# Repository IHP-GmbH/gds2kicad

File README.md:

# gds2kicad

Turn a die or chiplet GDSII into the KiCad parts you need to design a board or
an interposer around it: footprints, schematic symbols, pin lists, and the
netlist that flows back into the chiplet assembly format.

KiCad cannot read GDS. The usual fallback is redrawing bond pads by hand from a
datasheet and typing pin names into a symbol cell by cell, then doing it again
every time the layout changes. gds2kicad reads the pad geometry and the text
labels straight out of the layout, so the KiCad part matches the silicon.

## Status

> [!WARNING]
> gds2kicad is currently a preview release only!

**Contents:** [Install](#install) - [Quick start](#quick-start) -
[Tools](#tools) - [Selecting layers](#selecting-layers) -
[Workflows](#workflows) - [Where files are written](#where-files-are-written) -
[Troubleshooting](#troubleshooting) - [Documentation](#documentation)

## Install

There is nothing to build and nothing to install: run the scripts from the
clone root. You need KLayout (reads the GDS) and PyQt6 (for the GUI).

```sh
python3 -m venv venv && source venv/bin/activate
pip install -r requirements.txt    # PyQt6, PyYAML
pip install klayout                # GDS reader
```

A system KLayout install with its Python bindings on `PYTHONPATH` works too. If
`import klayout.db` fails, the converters exit with a message saying so.
`pip install -e .` installs the same modules with all three dependencies,
klayout included (`pyproject.toml`).

Python 3.11 is the version CI runs. On a slim Linux box or container, PyQt6 also
needs `libgl1 libegl1 libxkbcommon0 libdbus-1-3 libfontconfig1 libglib2.0-0`, or
the GUI dies on a Qt platform-plugin error. To run the tests you additionally
need `pip install pytest`.

## Quick start

No GDS at hand? Both converters can write themselves a small one, which is the
quickest way to check the install:

```sh
python3 gds_to_kicad.py --generate-test-gds     # writes tests/test_footprint.gds
python3 gds_to_kicad.py tests/test_footprint.gds -o demo.kicad_mod
```

That gives you 3 pads. They come out numbered, not named, because the fixture
carries no text labels; a real GDS does.

### With the GUI

The simplest way in, and it drives the same engine as the command line:

```sh
python3 unified_gui.py
```

One window, five tabs in order: **Extract Pins** from a GDS, **Pin List Editor**
to fix names, sides and types, **Symbol Designer** with a live preview,
**Footprint Generator**, and a **History** of past runs.

On a headless machine, set `QT_QPA_PLATFORM=offscreen`.

### From the command line

```sh
python3 gds_to_kicad.py die.gds -o die.kicad_mod          # footprint
python3 gds_to_kicad_symbol.py die.gds -o die.kicad_sym   # symbol
```

With no layer flags both tools auto-detect the densest pad layer and the text
layer that names the pads. That works on a clean chiplet GDS. On a real full die
it will happily return routing, fill and guard rings as "pads", so read
[Selecting layers](#selecting-layers) and
[Curating pads by hand](#curating-pads-by-hand) before trusting the result.

## Tools

| Tool | Does |
| --- | --- |
| `unified_gui.py` | GUI covering the whole flow: pins, symbol, footprint |
| `gds_to_kicad.py` | GDS to `.kicad_mod` footprint |
| `gds_to_kicad_symbol.py` | GDS to `.kicad_sym` symbol library |
| `blackbox_chiplet.py` | Pad map (JSON or CSV) to a stand-in GDS |
| `footprint_to_pinlist.py` | `.kicad_mod` to pin list JSON |
| `kicad_netlist_to_chiplet.py` | KiCad `.net` to chiplet YAML, CSV or `.chiplet` |
| `chiplet_to_kicad_sch.py` | `.chiplet` system to a KiCad schematic, one symbol per die and per carrier pad, or to a symbol library and blank sheet |
| `kicad_sch_to_connectivity.py` | Netlist of an edited system schematic to a connectivity form |
| `kicad_sch_to_cosim_setup.py` | Netlists of edited co-simulation setup sheets to a setup form |
| `extract_padmap.py` | Plan a die's pad map, or extract it from a finished die GDS |
| `io_pads/generate_io_pad.py` | Parametric interposer I/O pad symbol and footprint |
| `io_pads/kicad_pcb_to_iopads.py` | Routed `.kicad_pcb` to `io_pads.json` |

Every tool accepts `--help`.

## Selecting layers

There is no PDK baked in, no `--pdk` flag and no PDK discovery. You always say
explicitly where the pads are, in one of three ways:

| Precedence | How | Example |
| --- | --- | --- |
| 1 | Raw GDS number, ignores the `.lyp` | `--pad-layer-number 134/0` |
| 2 | Layer name from a KLayout `.lyp` | `--lyp-file pdks/sg13g2.lyp --layer TopMetal2.drawing` |
| 3 | Nothing, auto-detect the densest pad layer | (no flags) |

Pin names come from a separate text layer, selected the same way:
`--text-layer NAME`, `--text-layer-number N/D`, or auto-detect.

> **Two things that will bite you.** First, the flag spelling differs between
> the converters: `gds_to_kicad.py` uses `--layer`, `gds_to_kicad_symbol.py`
> uses `--pad-layer`. The `*-layer-number` flags are the same on both.
>
> Second, and this one costs people an afternoon: if you name the pad layer with
> `--layer` and say nothing about text, `gds_to_kicad.py` emits **numbered**
> pads instead of named ones, silently. Add `--text-layer NAME`, or
> `--auto-text` to let it find the text layer itself. The symbol tool does not
> have this problem: it derives `TopMetal2.text` from `TopMetal2.drawing` on its
> own, which is why it has no `--auto-text` flag. When both tools auto-detect
> the pad layer, both auto-detect the text layer too.

### Bundled layer files

`pdks/` ships four ready `.lyp` files:

| File | Contents |
| --- | --- |
| `generic.lyp` | **Default.** Pads-only vocabulary: pad metal `205/0`, pad text `205/25`, outline `206/0`. For closed chiplets that ship no layer file. |
| `sg13g2.lyp` | Full IHP SG13G2 layer set, a byte copy of IHP-Open-PDK's, pinned to its source commit by `tests/test_sg13g2_lyp_source.py` |
| `sky130.lyp` | Full SkyWater sky130 layer set, a byte copy of open_pdks' `sky130/klayout/sky130.lyp` (Apache-2.0) |
| `interposer.lyp` | SG13G2 upper metals through Bump, for interposer work |

Any technology works: drop its KLayout `.lyp` into `pdks/`, or pass any path
with `--lyp-file`. IHP SG13G2 is what we test against most, not a requirement.

### Inspecting a GDS first

```sh
python3 gds_to_kicad.py die.gds --scan-layers                        # suggest pad/text candidates
python3 gds_to_kicad.py die.gds --list-layers --lyp-file pdks/sky130.lyp   # dump the parsed .lyp
```

## Workflows

### Die to footprint

```sh
python3 gds_to_kicad.py die.gds --lyp-file pdks/sg13g2.lyp \
    --layer TopMetal2.drawing --text-layer TopMetal2.text -o die.kicad_mod
```

Reads the top cell, flattens it, pulls box and polygon shapes off the pad layer,
and names each pad from the nearest text label. Rectangular pads become
`smd rect`; non-rectangular pads become `smd custom` with a `gr_poly` primitive,
so the real shape is preserved. It also writes a courtyard and traceability
properties recording the source GDS, the `.lyp`, the layer and the orientation
(`GDS_FILE`, `LYP_FILE`, `GDS_LAYER`, `ORIENTATION`).

For a die that mounts face-down on an interposer, add `--flip-chip` to mirror X
so the footprint reads as seen from the interposer side.

Die thickness is assembly metadata, not GDS geometry, so it is only written when
you pass it: `--die-thickness-um 300` emits a `DIE_THICKNESS_UM` property that
chiplet-export reads into hyp-to-gds `--die-thicknesses` for the assembly z-stack.
Omit it and the property is left out (the export defaults it to 0.0).

By default the courtyard is the pad bounding box, which for an inset pad ring is
smaller than the die. Name the layer that carries the die outline, for example
`--die-outline-layer 206/0` for a generic black-box die or `189/4` (prBoundary)
for an SG13G2 die built with LibreLane, and the courtyard becomes that outline.
The layer is also recorded as a `DIE_OUTLINE_LAYER` property (`"206/0"`), meant
for downstream tools that size the die from its GDS rather than from KiCad
geometry. The outline must merge to exactly one rectangle containing every pad;
anything else, no pads at all, or a `--dbu` that differs from the file's is an
error and no file is written. Omit the option and neither the
courtyard nor the properties change.

### Die to symbol

```sh
python3 gds_to_kicad_symbol.py die.gds --lyp-file pdks/sg13g2.lyp \
    --pad-layer TopMetal2.drawing -o die.kicad_sym
```

Same pad and text extraction, emitted as a KiCad 6+ `.kicad_sym`. Pins are
arranged automatically: power top and bottom, signals left and right. Extras:
`--symbol-name`, `--footprint-ref`, and `--max-text-distance` (a DBU cutoff for
matching text to pads).

There is a two-step path when the automatic result needs fixing. Dump an
editable pin list, correct names, sides and types, then rebuild from it with no
GDS involved:

```sh
python3 gds_to_kicad_symbol.py die.gds --extract-pins pins.json
python3 gds_to_kicad_symbol.py --from-pin-list pins.json -o die.kicad_sym
```

In that JSON each pin carries a `name`, a `side` (`left`, `right`, `top`,
`bottom`) and a `type` (`passive`, `input`, `output`, `bidirectional`,
`tri_state`, `power_in`, `power_out`, `unspecified`), plus its geometry in DBU.
The same file is what the Pin List Editor tab edits, and what `--pin-list`
expects in the pad-review workflow below.

### Curating pads by hand

This is the normal path for real silicon, not an advanced fallback. A full die
GDS is mostly routing, fill and guard rings, and auto-detect cannot tell those
from bond pads. Strip the GDS down to the pad layer plus labels, clean it up in
KLayout, then build from the result:

```sh
python3 gds_to_kicad.py die.gds --generate-pad-review review.gds
klayout -e -l pdks/sg13g2.lyp review.gds   # delete everything that is not a real pad, save
python3 gds_to_kicad.py --from-pad-review review.gds --pin-list pins.json -o die.kicad_mod
```

`--pin-list` is **required** here: it is the authoritative list of names, and
pads are matched to it by nearest neighbor, with warnings for anything left
unmatched. Produce it with `gds_to_kicad_symbol.py --extract-pins pins.json` or
with `footprint_to_pinlist.py`.

To keep the die outline on this path, pass the same `--die-outline-layer` to
both steps. `--generate-pad-review` then copies the outline into `review.gds`
(leave it in place while editing), and `--from-pad-review` reads it back from
there, since that is the file the footprint's `GDS_FILE` names. Name the pad
layer explicitly on both steps (`--pad-layer-number` or `--layer`): the review
now holds two layers, and auto-detection may rank the outline first. Reading the
outline box as a pad is refused, with or without `--die-outline-layer`, rather
than turned into a single die-sized pad.

### A chiplet with no GDS

When you only have a pad map from a datasheet (names, centers, sizes) and no
layout and no layer file, synthesize a minimal stand-in GDS:

```sh
python3 blackbox_chiplet.py pads.json -o chiplet.gds
python3 blackbox_chiplet.py pads.csv  -o chiplet.gds --no-manifest
```

The spec is JSON or CSV, chosen by extension. CSV is a `name,x_um,y_um,w_um,h_um`
header with one pad per row; JSON adds an optional explicit `die` size and a
`chiplet_name`. Pad `x`/`y` are **center** coordinates. Without an explicit die,
the outline comes from the pad extents plus a margin.

Pads, labels and outline are stamped on the canonical generic layers
(`205/0`, `205/25`, `206/0`), so the output feeds the converters above with no
flags at all. Alongside the GDS it writes a `<stem>.boundaries.json` manifest
carrying the die outline as the chiplet boundary for assembly DRC; suppress it
with `--no-manifest`.

### Board back to chiplet netlist

```sh
python3 kicad_netlist_to_chiplet.py design.net --yaml nets.yaml --csv nets.csv
python3 kicad_netlist_to_chiplet.py design.net --inject board.chiplet --summary
```

Converts a KiCad S-expression netlist to YAML and/or CSV, or
injects a `netlist:` section straight into a `.chiplet` file. Nets are classified
power, ground or signal by name. Footprints from the `io_pads` library, or any
ref prefix you pass with `--external-ref-prefix J`, are flagged `external: true`.
Pass at least one of `--yaml`, `--csv`, `--inject` or `--summary`.

Going the other way, `footprint_to_pinlist.py` pulls pad geometry out of one or
more `.kicad_mod` files into a pin list JSON.

### System schematic from a chiplet

```sh
python3 chiplet_to_kicad_sch.py --chiplet design.chiplet \
    --pins U1=u1_pins.json --pins U2=u2_pins.json \
    --out sys.kicad_sch --report schematic.json --check
```

Draws the system as one KiCad 9 sheet: a symbol per die (Reference is the
component id), a pin per name in that die's pin list (number is the pin name,
label is its `port`), and a global label with the exact net name on every
connected pin. A name the list repeats, one pad of a rail, is drawn as one pin.
Terminals on no net get a no-connect flag, except open pins that link dies,
which are left bare so KiCad's list of unconnected pins is the list still to
wire. Nets come only from the `.chiplet`,
so the sheet is a view of the description, not a second source of it.

The sheet is laid out to be read and wired on paper, not to mirror the pads.
The dies sit in one row in `.chiplet` order, and every pin is on the left or
the right of its symbol, so every name reads horizontally. A die's link pins
(open, or on a net that joins dies and nothing else) face its neighbour, the
first die's on its right and the others' on their left; power pins, carrier
nets and nets of one die take the other side. Each column runs in port order
with numbers read as numbers (`d2d_f2` before `d2d_f10`), so two dies with the
same port names line up row for row, and the link side keeps room for a label
on every pin, so a sheet with its links open and the wired one share a layout.

A carrier (a component that is not a die but lists `io_pads`, such as a
wire-bond interposer) is drawn as its pads, in a column below the dies in name
order: one `chiplet_system:EXT_PAD` symbol per pad, the symbol designer sheets
use, with Reference initially the pad id, hidden `IO_PAD_ID` the stable pad id,
`CHIPLET_COMPONENT` the carrier id and
Footprint `chiplet_carrier:EXT_PAD_<n>um` from the pad's `.chiplet` size. The
pad's net is the one the netlist connects it to, else its `io_pads` net, else
none. A die symbol's Footprint is `chiplet_dies:<top cell>`, so a board the
export drew pairs with the sheet symbol for symbol. The carrier's pin list keeps the edge
each pad sits on; it is derived from the `.chiplet` and written next to the
sheet as `<id>.carrier_pins.json`, and the report records it like a die's.
Reading the sheet back (`--check`, `kicad_sch_to_connectivity.py`) folds a
carrier's pads into one carrier symbol whose pins are the pad ids.
Read-back takes the pad id from `IO_PAD_ID`, so Annotate can change a pad's
Reference without changing its terminal. Older sheets where every pad has an
absent or empty field use Reference as before. If any carrier pad has the
field, all must; a missing field is refused as `missing_identity`, naming its
carrier and Reference. Two pads of one carrier with the same pad id are refused
as `duplicate_pad`, naming both References, and neither folds.
Shared References are refused as `duplicate_reference` in every sheet mode
and by `--check`. The placed UUIDs distinguish pasted copies from distinct
units of one library symbol; an unresolved UUID is an input error.
A generated die-library symbol missing `CHIPLET_COMPONENT` is refused as
`missing_identity`; parts from other libraries keep a null identity.

Each symbol carries a hidden `CHIPLET_COMPONENT` property with its component
id, and title-block comment 1 holds the sha256 of the `.chiplet` it was drawn
from; reruns on the same inputs are byte-identical. Anything that cannot be
drawn verbatim is refused by name and no sheet is written: a connection to a
component that is neither a die nor a carrier, a pin the component does not
have, a pad whose netlist net and `io_pads` net disagree, a pad `io_class`
outside the format's vocabulary, a pad whose size is missing, not square or not
a whole number of um, a pad id that is also a component id or another pad's, a
die that states no top cell, a die or carrier id outside `[A-Za-z0-9_.+-]`,
or a pin or net name outside that set plus numeric subscripts after the first
character (`IO[0].pad` is drawn; KiCad gives other characters meaning, reads
`B[0..3]` as a bus and a pin `[0]` as stacked pins). The report lists every refusal. `--check` exports the
sheet's netlist with `kicad-cli` and compares it with the `.chiplet`. Exit
status is 0 when written, 3 when refused, 4 when written but the check found a
difference or could not run.

With `--setup cosim.setup.json --setup-spec cosim_setup_symbols.json`, a
co-simulation setup projection (`chiplet_cosim.cosim_setup` 1.0) and the symbol
spec the co-simulation flow draws it with (`chiplet_cosim.cosim_setup_symbols` 1.0; pass
your own, the copy under `tests/fixtures/` is only for the tests), the setup is drawn too: its system-sheet
symbols (simulation, models, supplies, crossings, bench) in a band below the
dies, and its die, bench and channel sheets as flat sheets of their own beside
the system sheet (`sys.die.<die>.kicad_sch`, `sys.bench.kicad_sch`,
`sys.channel.<net>.kicad_sch`), each netlisted on its own. A setup symbol
carries a `chiplet_cosim_setup` field holding its kind and one field per
attribute, and is excluded from simulation and from the BOM. Bench and channel
elements are R, C and L primitives and DC or pulse V and I sources, each with
its SPICE name as Reference and drawn as a raw SPICE model. KiCad writes a raw
model's text into the card unchanged only when it is digits and points, and any
other number to six significant digits, so an R, C or L model is the value's
exact plain decimal (`2.322105e-14` as `0.00000000000002322105`) while its Value
shows the projection's text. A value typed in e-notation with more than six
significant digits is rounded by KiCad, and the reader refuses it
(`value_rounded`): type a plain decimal, or six digits at most. The title block
of each bench and channel sheet says so.
A reference without a trailing digit (`VSEL`) is one KiCad reports as not
annotated; annotating renames it, which co-simulation reads as an edit, and the
sheet's title block says so. The report names the projection and the spec by
sha256 and lists every setup sheet by role, path and sha256; the check leaves
setup symbols out.

Beside the sheets go the symbol library `chiplet_cosim.kicad_sym` and a project
`sym-lib-table` naming it `chiplet_cosim`, so a setup symbol of any kind whose
pins the spec fixes can be placed from KiCad's symbol chooser, also a kind the
case does not use (a probe on a die sheet that has none). A placed symbol
carries its kind and one empty field per required attribute, to fill in; an
optional attribute is a field to add by hand. Each library symbol is the one
the sheets embed for its kind. The bench and block kinds take their pins from
their row, so the library has no symbol for them:
to place one, copy an existing one. A `sym-lib-table` already in the output
directory is refused unless it is the one the generator writes; the report
lists the library and the table by path and sha256.

A system whose dies have no pin lists (a mixed co-simulation case) is drawn with
`--setup-only` instead of `--pins`: no system sheet is written, and the
system-sheet setup symbols go on a flat sheet of their own,
`sys.system.kicad_sch`, beside the others. The .chiplet only names the system;
`--check` does not apply, and the report's `schematic` is null.

`kicad_sch_to_cosim_setup.py` reads the edited setup sheets back. It takes the
generator report, the form to write, and `--sheet SCHEMATIC NETLIST [SPICE]` once
per sheet: the kicadsexpr netlist and, for a bench or channel sheet, the SPICE
netlist, both exported with kicad-cli. It writes `chiplet_cosim.cosim_setup` 1.0
with tool `kicad`: every setup symbol with its kind, attributes and pins, each
pin open or on its net as KiCad named it, and every sheet and SPICE netlist by
path and sha256. It reads the SPICE netlist only to check it: every R, C, L, V
or I card must carry, as numbers, the value its symbol's fields state, or the
sheet is refused as `value_rounded` (a standard part whose value KiCad rounded,
or a Value edited on a raw model that KiCad does not read). An attribute left
empty, as a field of a placed library symbol is until someone fills it in, is
refused as `attribute_empty`. Otherwise it judges nothing; the co-simulation
flow's back end does. Exit status
is 0 when written and 2 when an input is not what it claims, with no form
written.

Once the sheet has been edited, `kicad_sch_to_connectivity.py` reads it back:

```sh
kicad-cli sch export netlist --format kicadsexpr --output sys.net sys.kicad_sch
kicad-cli sch erc --format json --severity-all --output erc.json sys.kicad_sch
python3 kicad_sch_to_connectivity.py sys.net sys.kicad_sch schematic.json \
    connectivity.json --erc erc.json
```

It writes the connectivity form (`chiplet_system.connectivity` 1.0) a schematic
import turns into a `.chiplet` revision: each symbol with its
`CHIPLET_COMPONENT` identity and pin numbers, each net with its endpoints and
whether KiCad made its name up, the base digest from the title block, and the
report, netlist, sheet and ERC report by path and sha256. It only reports what
KiCad resolved; judging the edit is the import's job. What the form cannot
carry is listed as a refusal in it: a hierarchical sheet, a net named by a
local label, two names on one net (from the ERC report), or a node on a pin its
symbol does not have. A co-simulation setup symbol (a non-empty
`chiplet_cosim_setup` field) is left out with its pins, so setup symbols never
change the form. `--no-erc` skips the ERC report and with it the two-name
check. Exit status is 0 when the form is written, refusals included, and 2 when
an input is missing or is not what it claims to be.

#### Drawing the system on a blank sheet

For an exercise where the connections are drawn by hand, `--handout DIR`
writes, instead of a sheet, what is needed to draw one from scratch:

```sh
python3 chiplet_to_kicad_sch.py --chiplet given.chiplet \
    --pins U1=u1_pins.json --pins U2=u2_pins.json --handout sheet_first/
```

`DIR` gets `chiplet_dies.kicad_sym`, a `sym-lib-table` naming it
`chiplet_dies` through `${KIPRJMOD}`, and a project with an empty sheet, both
named after the `.chiplet` (or `--name`). The library has one symbol per top
cell, named by it, with Reference prefix `U`: the drawing of the sheet above
with the link pins always on the right and every pin passive. It carries no
`CHIPLET_COMPONENT` property, and no file carries a digest, a time or a host
path, so two runs give the same bytes. Carriers are not drawn. A die whose top
cell is not a plain name is refused, and so are two dies of one top cell that
would need two different symbols.

The same handout can be drawn from die folders, with no `.chiplet`
(`die_handout.py`). Each folder holds `die-contract.json` and the inventory it
binds, and lies inside the handout directory: a placed die's `Die` field is
that folder, relative to the folder of the `.chiplet` source, so keep that
source in the handout directory. A folder is read as the classic import
reads it, so a die whose contract and inventory name different pads, or with a
pad on no port, is refused rather than drawn. One symbol per top cell, and one
folder per top cell. There is no system netlist, so a link pin is not drawn
apart from any other signal: signals sit on the right, power and ground on the
left. `chiplet_system.kicad_sym` holds `GND`, `SUPPLY` and `EXT_PAD`. The table
names `chiplet_system` first, then `chiplet_dies`. `--ext-pad-um` is the
external pad's edge in whole micrometres. The project name is `--name`, or the
output directory's own name. A die whose repeated pad numbers are all one power
or ground port gets `duplicate_pin_numbers_are_jumpers` on its symbol; any other
repeat is refused as `undeclared_tie`. KiCad 9.0 cannot read that flag, so such
a handout opens only in the tools image's KiCad. A handout drawn from a
`.chiplet` never sets it, so a die whose rail pads repeat a number, drawn that
way, is refused at interposer-pnr `export --form`; that is expected, draw it
from its die folder instead.

```sh
python3 chiplet_to_kicad_sch.py --handout sheet_first/ \
    --dies sheet_first/dies/DRIVER --dies sheet_first/dies/ECHO --ext-pad-um 80
```

The drawn sheet is read back with `--blank --library sheet_first/chiplet_dies.kicad_sym`
in place of the generator report (`NETLIST SCHEMATIC OUT_FORM`). That writes
form 1.1 with `sheet` set to `blank`: no base digest and no report, the library
by path and sha256, and each symbol's `part` (library nickname and symbol name)
with its identity null. Two symbols under one reference, such as two left
unannotated, are refused as `duplicate_reference`. Without `--blank` the form
stays 1.0.

For a classic sheet drawn from die folders, read both handout libraries:

```sh
python3 kicad_sch_to_connectivity.py sys.net sys.kicad_sch connectivity.json \
    --classic --library sheet_first/chiplet_dies.kicad_sym \
    --system-library sheet_first/chiplet_system.kicad_sym --erc erc.json
```

This writes form 1.2 with `sheet` set to `classic`, each symbol's UUID key,
value, footprint and all fields verbatim, no-connect flags as `open`, and
`rails` from the root sheet's `chiplet_system:GND` and `chiplet_system:SUPPLY`
symbols. A supply's `Volts` is empty or a plain decimal above zero. Multi-unit
symbols, net-naming power symbols from another library (a PWR_FLAG names no
net and is ignored), invalid or conflicting rail voltages, and
rails absent from the netlist are refused. Refused rails are omitted from the
rail list. A rail name follows KiCad net-name escaping. Symbols sharing a
reference retain separate UUID records and their own properties, so the import
can diagnose the duplicate. Hierarchical sheets are refused with only root
symbols written. The generated and blank modes keep their existing formats.

### Interposer I/O pads

```sh
python3 io_pads/generate_io_pad.py --io-class wire_bond --size 100x100
python3 io_pads/kicad_pcb_to_iopads.py design.kicad_pcb -o io_pads.json
python3 io_pads/kicad_pcb_to_iopads.py draft.kicad_pcb --export-report export.json -o io_pads.json
```

`generate_io_pad.py` emits a parametric KiCad symbol and footprint for an
external interposer pad, tagged with `IO_CLASS` and `IO_PAD_SIZE_UM` properties.
Only `wire_bond` is implemented today; `flipped_bump` and `tsv_bump` are
reserved and rejected.

After routing, `kicad_pcb_to_iopads.py` walks the `.kicad_pcb`, keeps the
footprints carrying an `IO_CLASS`, and writes pad locations, sizes and nets to
JSON (mm to um, Y negated for the GDS Y-up convention). Each pad's `ref` is its
io_pad id: on a board interposer-pnr `export` drew (carriers from
`chiplet_carrier` or carrying `IO_PAD_ID`) its `IO_PAD_ID`, which every carrier
there must carry, else the Reference. Each `net` is the planner's name: a board
drawn against a sheet needs `--export-report`, the report `export` wrote, to
map its sheet nets back, and a board whose carriers link sheet symbols is
refused without one. Full library setup is in
[io_pads/README.md](io_pads/README.md).

## Where files are written

From the **command line**, generated files land in the current directory:
footprints under `generated_kicad_footprint_files/`, symbols under
`generated_kicad_symbol_files/`.

| To control it | Use |
| --- | --- |
| Exact output path | `-o FILE` |
| Per-design `<DIR>/<design>.pretty/` convention | `--design-dir DIR` (footprint tool only) |
| Different base directory | `GDS_TO_KICAD_DATA_DIR` environment variable |

The **GUI** works differently: every export goes through a save dialog that
starts in the directory you launched the GUI from. Only the conversion history
registry is written under `generated_kicad_symbol_files/`.

One more: `io_pads/generate_io_pad.py` writes back into your clone
(`io_pads/kicad_symbols/`, `io_pads/kicad_footprints/`) unless you pass
`--out-dir`.

## Troubleshooting

| Symptom | Cause |
| --- | --- |
| `No module named klayout` | `pip install klayout`, or put a system KLayout's bindings on `PYTHONPATH` |
| Qt "xcb platform plugin" error on Linux | Missing Qt system libraries, see [Install](#install); or use `QT_QPA_PLATFORM=offscreen` |
| Footprint pads come out numbered, not named | You passed `--layer` but no text layer; add `--auto-text` or `--text-layer` |
| Thousands of pads, huge output file | Auto-detect grabbed routing or fill; use [pad review](#curating-pads-by-hand) |
| `pdks/...lyp` not found | The examples use paths relative to the clone root; run from there or pass an absolute `--lyp-file` |

## Documentation

- [io_pads/README.md](io_pads/README.md), the I/O pad library workflow.
- `--help` is authoritative for flags; this README covers the common paths.

Tests (needs `pytest` and `PyYAML`, see [Install](#install)):

```sh
QT_QPA_PLATFORM=offscreen pytest tests -q
```

`-ra` (on by default, see `pyproject.toml`) prints the reason for each skip.
The ones to expect:

- two need the IHP PDK (`PDK_ROOT`): they compare the vendored `pdks/sg13g2.lyp`
  and the pad layers against the PDK's own layer sheet;
- twenty, all in `tests/test_netlist_converter.py`, look for a demo netlist and
  `.chiplet` under `kicad_designs/kicad_interposer_hyperlynx_to_gds/chiplet_files/`,
  and that directory is empty: those cannot run anywhere today, here or in CI.
  Either vendor the two small fixtures into `tests/` or drop the tests; do not
  read their skip as an environment problem.

The cases that run the real `kicad-cli` are deselected by default, so a bare
`pytest` starts no external tool. Run them with `pytest -m kicad_cli`; with
`GDS_TO_KICAD_REQUIRE_KICAD_CLI=1` a missing `kicad-cli` is a failure instead of
a skip.

Upstream: [github.com/IHP-GmbH/gds2kicad](https://github.com/IHP-GmbH/gds2kicad).

## License

GPL-3.0-or-later. See [LICENSE](LICENSE). The copy in `_vendor/chiplet_format_io` is Apache-2.0 (`LICENSES/Apache-2.0.txt`), inside this GPL-3.0-or-later tool; `_vendor/chiplet_format_io.SOURCE` names the chiplet-spec commit it was copied from and each file's sha256.

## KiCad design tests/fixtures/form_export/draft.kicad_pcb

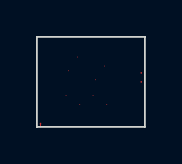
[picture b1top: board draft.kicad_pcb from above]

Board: 4 copper layers, 6.0 x 5.0 mm, 7 parts (0 on the bottom side), 2 nets.

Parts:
D_FLIP: CELL_D_FLIP
D_FR: CELL_D_FR
D_ROT: CELL_D_ROT
D_UP: CELL_D_UP
J1, J2, J10: EXT_PAD_80um

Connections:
OUT: D_UP.A0, J1.1
vss: D_FLIP.A1, J2.1, J10.1

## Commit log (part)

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2026-02-21 Consolidate symbol, footprint, and shared into single repo
    Merges gds_to_kicad_symbol/, gds_to_kicad_footprint/, and shared/
    into a flat layout. All shared modules are now real tracked files
    instead of symlinks. The unified GUI imports footprint code directly
    instead of via importlib dynamic loading.
    Previous histories:
    - gds_to_kicad_symbol: 10 commits (f518034..358edf1)
2026-02-23 Add dynamic DBU detection from layout.dbu
    Replace hardcoded DBU_TO_MM = 1e-6 with runtime detection via
    layout.dbu. Supports explicit --dbu override for cases where the
    GDS metadata is wrong. Affects convert(), convert_from_pad_review(),
    bounding box display, and footprint generation.
2026-02-23 Add cross-reference thumbnails between symbol and footprint tabs
    Symbol tab now shows a pad layout thumbnail with pad count.
    Footprint tab shows a symbol thumbnail with pin count. Both
    display a mismatch warning when pin and pad counts differ.
2026-02-23 Simplify workflow: edit GDS before extraction, remove pad review
    Replace the old workflow (extract -> pad review -> sync back) with a
    simpler one: generate stripped GDS, edit in KLayout, then extract from
    the cleaned file. This eliminates bidirectional sync complexity.
    Changes to unified_gui.py:
    - Add "Prepare GDS for Extraction" section to Tab 1 with generate/open
    buttons for stripped and full GDS files
2026-02-23 Fix stripped GDS text: don't pass empty pin_list to generate()
    _sync_editor_to_pin_list() creates an empty PinList when none exists,
    so pin_list was never None when reaching PadReview.generate(). The
    pin_list branch wrote zero labels since there were no pins. Now we
    pass pin_list=None when it has no pins, allowing the text_layers
    copy-from-source path to execute.
2026-02-23 Add explicit extraction source selector (Full GDS / Stripped GDS)
    Replace the implicit auto-detection with a combo box so users always
    know which GDS file the extraction will read from. The Stripped GDS
    option is disabled until one is generated, then auto-selected.
2026-02-23 Improve GUI layout for Symbol Designer and Footprint Generator tabs
    Tab 3: replace fixed-height cross-ref with a resizable vertical splitter,
    give more space to preview side (400/600 ratio). Tab 4: remove group box
    wrapper and height cap on symbol thumbnail so it fills available space.
    Both preview widgets now allow smaller minimum sizes (200x150) to not
    block splitter dragging.
2026-02-23 Fix log panel unrecoverable after dragging splitter to zero
    Set minimum height on log widget (30px) so the header row with the
    Show/Hide button always stays visible. Disable collapsible on the
    log panel so the splitter respects the minimum height. Toggle button
    also restores the splitter to a usable size when clicked.
2026-02-23 Sequential pin numbers, vertical text, and absolute footprint paths
    Pin numbers are now sequential integers (1, 2, 3...) instead of
    repeating the pin name, matching standard KiCad convention. Footprint
    pad names follow the same scheme. Top/bottom pin names in the symbol
    preview render vertically to avoid overlap. Footprint GDS_FILE and
    LYP_FILE properties now store absolute paths, and GDS_FILE points to
    the full GDS rather than the stripped one.
2026-02-23 Hide pin numbers and widen top/bottom pin spacing
    Pin numbers are hidden in the .kicad_sym output since number==name
    makes displaying both redundant. The number is still stored for
    netlist/footprint matching but not rendered visually.
    Top/bottom pins now use 5.08mm horizontal spacing (2x standard) to
    give vertical text labels room to breathe. Left/right pins keep the
    standard 2.54mm vertical spacing. Character width estimate bumped to
2026-03-18 Add schematic wiring helper for global label placement
    Computes world coordinates from symbol positions + pin offsets
    and injects global_label S-expressions into KiCad schematics.
2026-03-18 Add KiCad netlist to chiplet YAML/CSV converter
    Parses KiCad S-expression netlists and outputs both YAML (for
    .chiplet files) and CSV (for Netlist::import_csv()). Supports
    net classification by name heuristics, layer mapping, and
    injection into existing .chiplet files.
2026-03-23 feat: add footprint_to_pinlist.py for extracting PinList JSON from .kicad_mod
    Parses pad entries from KiCad footprints and generates PinList JSON
    compatible with bump_mirror.py. Handles KiCad y-down to GDS y-up
    coordinate conversion. Supports batch mode for multiple footprints.
2026-04-30 Mark nets touching I/O pads as external in netlist converter
    kicad_netlist_to_chiplet.py now walks the (components) section of the
    KiCad netlist and identifies external I/O pad components by their
    footprint library (default: io_pads, matches the library produced by
    gds_to_kicad/io_pads/). Every net touching such a component is flagged
    external: true in the emitted YAML.
    Closes the netlist half of the wire-bond infrastructure: the .chiplet
2026-05-29 Add --design-dir flag for per-design footprint output
    Routes footprints to <DIR>/<design>.pretty/ (KiCad library convention)
    via a new resolve_footprint_output() helper. Default and -o/--output
    paths are unchanged. Adds unit and CLI tests.
2026-05-31 feat: add black-box chiplet GDS generator
    blackbox_chiplet.py synthesizes a chiplet GDS (die outline + metal pads +
    pad names) from a simple JSON/CSV pad list, stamped on the ADK canonical
    generic layers (pad_drawing 205/0, pad_text 205/25, outline 206/0), with the
    die outline mirrored onto exchange0 (190/0) so the assembly DRC and hyp_to_gds
    see the boundary.
    The output flows unchanged through the bare footprint converter, which
2026-05-31 refactor: generic.lyp is hand-maintained, add canonical-vocabulary drift test
    The ADK no longer generates generic.lyp (the Jinja generator was dropped as
    over-engineering for a 3-layer static vocabulary). adk/config/chiplet_pads.json
    stays the single source of truth; this committed lyp is now hand-maintained and
    a drift test pins its numbers to load_canonical_layers().
2026-06-01 gds_to_kicad: blackbox emits boundary manifest, stops stamping exchange0 190/0
    The black-box generator mirrored the die outline onto exchange0 (190/0), a real
    IHP fab layer. That double-stamped when the die was placed by hyp_to_gds (which
    also stamped 190/0) and could alias chiplet-internal geometry on that layer.
    Write the die outline as the chiplet boundary in a <stem>.boundaries.json
    manifest (die-local DBU, identity transform) instead. Drop exchange0 from the
    canonical layers and replace --no-exchange0 with --no-manifest. The outline
2026-06-03 symbol converter: black-box / default-LYP support
    Mirror the footprint converter's black-box path in the symbol converter so a
    closed-PDK chiplet GDS (pads + names, no .lyp) round-trips to a .kicad_sym.
    - pin_extractor: extract_named_pads_raw addresses pad/text layers by raw
    (layer, datatype) instead of LYP names, reusing the existing
    extract_pads/extract_texts/associate_texts_with_pads path.
    - gds_to_kicad: resolve_pad_layer reads the pad-name flag under either --layer
2026-06-10 blackbox_chiplet: ADK discovery walk with repo alias, manifest schema pin
    _adk_root now follows the ecosystem discovery convention: explicit arg,
    then $ADK_ROOT validated against config/chiplet_pads.json (set-but-invalid
    falls through), then an upward sibling walk over adk/ first and the GitHub
    repo name ADK/ second. Previously a GitHub-named checkout never resolved
    and the tool silently fell back to hardcoded layers.
    The boundary-manifest writer points at adk/docs/boundary_manifest.md and a
2026-06-11 Write generated files and registry to the working dir, not the install dir
    The GUIs anchored their output, library and registry paths to
    Path(__file__).parent. In the adk-tools image that's the read-only
    /opt/adk-tools tree, so the footprint converter crashed at startup as the
    non-root user when it tried to mkdir the registry parent.
    Resolve a writable base instead -- the working dir, overridable with
    GDS_TO_KICAD_DATA_DIR -- through a shared _paths.resolve_data_dir(). Under the
2026-06-18 Add GPL-3.0-or-later LICENSE and SPDX headers (#1)
    gds_to_kicad imports klayout.db in-process, making it a derivative work of
    KLayout (GPLv3); it previously shipped with no LICENSE file at all. Add the
    GPL-3.0-or-later license text and per-file SPDX-License-Identifier headers.
2026-06-18 docs: feature the unified GUI with a screenshot
    Promote unified_gui.py to its own section in the README and docs/README as
    the recommended, no-flags way to use the suite, and add a Symbol Designer
    screenshot (docs/img/unified-gui.png).
2026-06-20 Escape untrusted names in KiCad and .chiplet output
    GDS text labels, cell names and netlist names are interpolated into the
    generated .kicad_mod, .kicad_sym and .chiplet files; a stray quote, paren
    or newline corrupted the output, and a net name with ':' or '#' broke the
    injected YAML or silently changed its type.
    Add a shared sexpr token sanitizer (sexpr.py) and route the footprint
    cell/pad names through it; broaden the symbol sanitizer to parens, CR/LF
2026-06-20 Make .chiplet --inject robust: blank lines, atomic write, exit code
    The netlist-section replace regex only matched 2-space-indented lines, so a
    blank line inside the netlist block ended the match early and orphaned the
    remaining nets into the freshly written section (stale nets silently merged
    into the new netlist). Match indented OR blank lines and stop at the next
    column-0 key.
    Rewrite the target via a sibling temp file + os.replace so an interrupted or
2026-06-20 Write outputs atomically as UTF-8
    Every text writer opened the final path directly with the platform-default
    encoding, so a mid-write failure (ENOSPC, interrupt, encode error) left a
    corrupt partial .kicad_mod/.kicad_sym/.boundaries.json/.chiplet at the
    canonical path, and a non-ASCII pad/net name raised UnicodeEncodeError and
    truncated the file under a non-UTF-8 locale.
    Add a shared atomic_write() context manager in _paths.py (sibling temp file
2026-06-20 Fix pin/pad identity: dedup collisions, classifier drift, greedy matching
    - PinList.deduplicate_names checked only a per-name counter, so a synthesized
    suffix could equal an existing name ([A, A, A_1] -> two A_1). Check each
    candidate against every finalized name so the result is always unique.
    - VALID_PIN_TYPES was missing tri_state, a real PinType the writer emits and
    the layout accepts, so a tri-state pin spuriously failed validation.
    - symbol_layout sent VINN/VINP to the power side while the netlist classifier
2026-06-20 Tighten input validation and output hygiene
    - blackbox_chiplet: an incomplete die spec (width_um without height_um, or
    vice versa) silently fell through to pad-derived extents, recording a wrong
    boundary in the manifest; reject it with a clear error.
    - gds_to_kicad_symbol: --max-text-distance 0 was truthiness-checked and
    silently became auto/None; test against None so an explicit zero cutoff is
    honored.
2026-06-20 Remove dead code and consolidate the triplicated GUI theme
    - Delete wire_schematic.py: orphaned one-off demo code hardcoded for a single
    schematic, referenced nowhere (no import, GUI, test or doc).
    - The footprint and symbol GUIs each carried their own identical copies of the
    Nord COLORS dict, the STYLESHEET and FilterableComboBox; import them from the
    shared theme.py instead (which unified_gui already used), removing ~540 lines
    of duplication that previously let the three copies drift apart. Drop the

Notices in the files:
README.md:
License:
GPL-3.0-or-later. See [LICENSE](LICENSE). The copy in `_vendor/chiplet_format_io` is Apache-2.0 (`LICENSES/Apache-2.0.txt`), inside this GPL-3.0-or-later tool; `_vendor/chiplet_format_io.SOURCE` names the chiplet-spec commit it was copied from and each file's sha256.
